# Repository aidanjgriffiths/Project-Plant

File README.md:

# Plantiful
#### A Powerful Embedded Monitoring Device for plant Enthusiasts
This page aims to document the source code, software and hardware incorporated in the development and production of the Plantiful prototype.

## Software
### Android Studio  
Used for developing a mobile app that will collect sensor data and provide information to the user regarding the state of their plants. 
Many people possess Android phones. Group members have experience programming in Java on this platform. 
### PHP Storm  
Modern PHP IDE for developing Web Applications within several Web Environment's. This provides our Users with a Convenient platform for viewing Plant Data, with regard to the health status of their plants, the weekly requirements from the User in terms of providing the appropriate nourishments for the Plants, and the projected requirement's in the future.
### MySQL Workbench
Interface directly to the Database hosted in the cloud, allowing for effective and simple queries and modifications to the Database
### AWS Lightsail
Web Sever Hosting Service on Amazon Web Services, which hosts the Virtual Web Server, running a Headless Ubuntu Instance, with a LAMP (LAMP) stack pre-installed on the operating system  
### AWS MySQL RDS
Relational Database Service for the Cloud MySQL Database, for access from the Web Application and Android Application. This is the central point for the back-end configuration of the MySQL Database Instance
### Arduino IDE 
IDE provides a coding platform for writing high level C/C++ based code that can be flashed to an Arduino board. 
Accessible coding platform. Runs on Windows. Basic setup and looping format. Many well-established libraries available. USB flashing. Debugging is simple using the provided serial terminal.
### AutoDesk Fusion 360 
Used for developing 3D designs for the hardware enclosure (prototype and final design). 
Accessible. At least one group member has experience developing models with this software. Parts can be assembled and animated. Enable direct export of 3D printing file. Schematic drawings are available for large scale production. 
### AutoDesk Eagle
Used for developing CAD schematic and printed circuit board designs for the embedded system final design. Program works in conjunction with Fusion 360 to purpose fit to the hardware shell.
### Cura 
Enables slicing and positioning of component pieces on 3D printing platform. 
Group member is in possession of this software and has experience using it for printing prototypes. 

## Hardware
### Uno R3 
Compact micro-processing unit with I/O ports for interfacing with moisture, temperature/humidity and light sensors. Minimal processing required except to transmit sensor data serially over Bluetooth.
Accessible, cost effective, and comes with an IDE that includes simplified coding functions for reading data from sensors and communicating serially with the proposed mobile application. Used for initial development, with later revisions using the same microcontroller (ATMEL ATMega328) in a bare configuration. 
### Moisture sensor 
DFRobot moisture sensor measures soil moisture, utilising an inbuilt transistor and associated discrete parts amplify a weak current between the probes into a 0-5v signal dependent on moisture. Will be used to determines if plant requires watering or is over-hydrated. 
Cheap, accurate and interfaces well with Arduino. No external libraries are required. 
### Temperature / Humidity sensor (DHT12)
Digital temperature and humidity sensor to determine ambient environmental parameters that determine the suitability of the conditions for optimal plant development. Highly reliable and fast response. -40 - 80C temperature range with error of +/- 0.5C, 0-100% humidity range with an error of 2-5% over the range. Easy to interface with Arduino with easy to use, highly available external libraries.
### Ambient light sensor (5kOhm Light Dependent Resistor)
Measures ambient light and reflects analog voltage to Arduino controller. Will be used to determine if the plant is receiving the correct amount of sunlight. 
Simple to use and interfaces relatively easily with Arduino requiring a single pull-up resistor as the only extra part. No additional libraries required, but basic calibration required.
### HC-05 Bluetooth module 
Enables Bluetooth connection with mobile device to communicate sensor data serially. 
Easy to setup and maintain a reliable connection with a mobile phone. Security is not a priority given the non-critical nature of the sensor data collected.

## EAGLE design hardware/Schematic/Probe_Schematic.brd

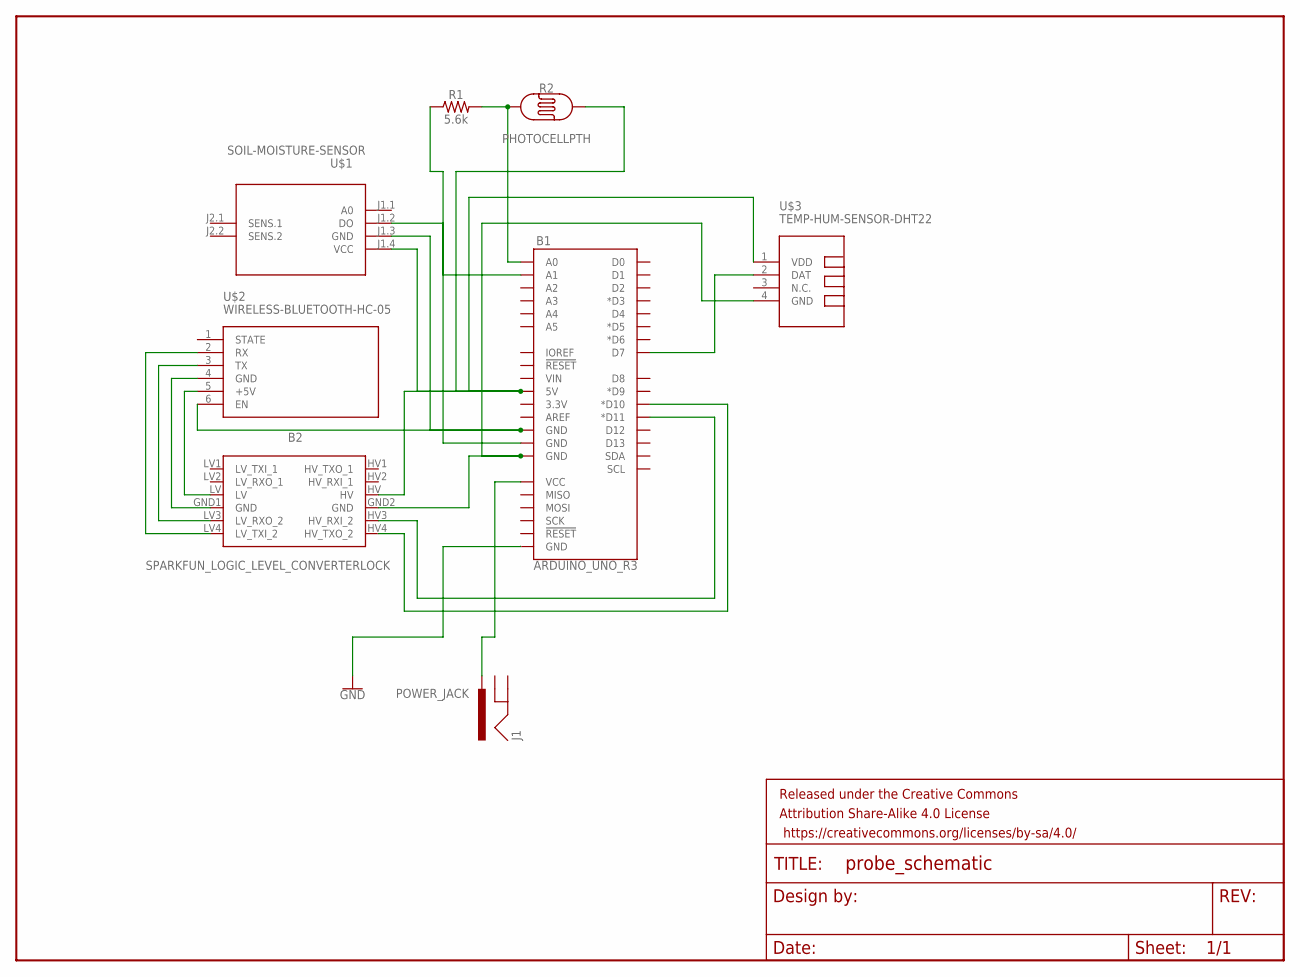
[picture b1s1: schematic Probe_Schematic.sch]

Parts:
B1: ARDUINO_UNO_R3; ARDUINO_R3
B2: SPARKFUN_LOGIC_LEVEL_CONVERTERLOCK; SPARKFUN_LOGIC_LEVEL_CONVERTER_LOCK
FRAME1: FRAME-LETTER; CREATIVE_COMMONS
J1: POWER_JACK; POWER_JACK_PTH
R1: 5.6k; 0603
R2: PHOTOCELLPTH; PHOTOCELL
U$1: SOIL-MOISTURE-SENSOR
U$2: WIRELESS-BLUETOOTH-HC-05
U$3: TEMP-HUM-SENSOR-DHT22

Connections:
GND: B1.GND@1 (GND)
unnamed: B1.GND@4 (GND), U$1.J1.3 (GND), U$2.6 (EN)
unnamed: B2.GND1 (GND), U$2.4 (GND)
unnamed: B2.LV, U$2.5 (+5V)
unnamed: B2.LV3 (LV_RXO_2), U$2.3 (TX)
unnamed: B2.LV4 (LV_TXI_2), U$2.2 (RX)
unnamed: B1.GND@2 (GND), B2.GND2 (GND), U$3.4 (GND)
unnamed: B1.GND@3 (GND), R1.1
unnamed: B1.D11 (*D11), B2.HV3 (HV_RXI_2)
unnamed: B1.D10 (*D10), B2.HV4 (HV_TXO_2)
unnamed: B1.D7, U$3.2 (DAT)
unnamed: B1.A1, U$1.J1.2 (DO)
unnamed: B1.VCC, J1.PWR
unnamed: B1.5V, B2.HV, R2.2, U$1.J1.4 (VCC), U$3.1 (VDD)
unnamed: B1.A0, R1.2, R2.1

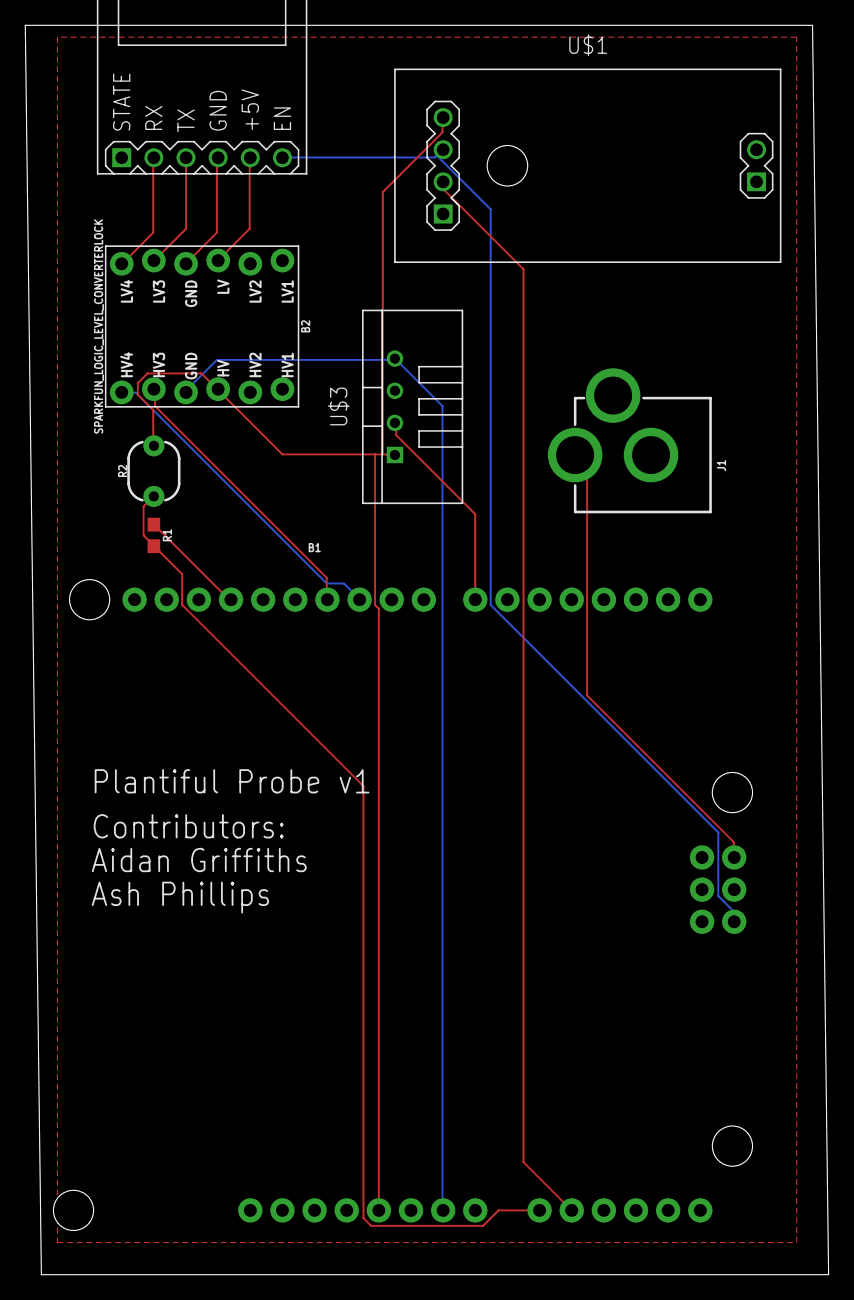
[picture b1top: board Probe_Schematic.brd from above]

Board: 2 copper layers, 63.5 x 98.7 mm, 9 parts (0 on the bottom side), 14 nets.

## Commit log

2020-08-07 Initial app commit
    Android app initial commit with splash screen, bluetooth connectivity and text-to-voice
2020-08-07 Added resources activity
    Links to 6 different resources on Australian flora
2020-08-07 Update AndroidManifest.xml
    updated the manifest to include the resources activity
2020-08-16 chore: Updated README Software and Hardware
2020-08-19 Added backend data base and monitoring
    Profiles and monitor activities added.
    Notification channel established for weekly notification to check on plants
    Camera, QR generator and reader included. Ability to add, delete profiles.
    Connecting to bluetooth shifted to montioring acitivity
2020-08-20 Information and help activities
    Added content to information and help activities
2020-08-23 FEAT: Add basic simulator functionality.
    Allow the generation of simulated values to help decouple the hardware and software development.
2020-08-26 chore: renamed several files to adhere to a consistent convention, removed unneccesary imports, redfined the file structure to improve consitency and design
2020-08-27 Testing and debugging
    Added camera permissions
2020-08-30 Added Main Structure of Plantiful Web
2020-08-30 Update README.md
    Added PHP Storm Blurb
2020-09-01 Added JQuery and QRCode Dependencies with Example
2020-09-03 Revert "chore: renamed several files to adhere to a consistent convention, removed unneccesary imports, redfined the file structure to improve consitency and design"
    This reverts commit 75622261d98e398c48d67b0120e4a7db74bda604.
2020-09-05 Added Database SQL Creation Script
2020-09-05 Added functionality to Establish the Database Connection
2020-09-05 Modified SQL Creation Script and Added Stored Procedures
2020-09-05 Removed Old DB Connector (DAL)
2020-09-06 Removed Unnecessary Files
2020-09-06 Modified SQL Creation Script to Support User Changes
2020-09-06 Modified User Model
2020-09-06 Added functionality for Android-Web Account Association
2020-09-06 Added Android Web API Test Application
2020-09-08 New Dev branch changes
2020-09-08 FEAT: Testers for invidual hardware components
2020-09-08 FEAT: First cut of main hardware sketch
2020-09-08 DOC: Bill of Materials
2020-09-08 FEAT: Initial hardware code
2020-09-08 Font Changes
2020-09-09 Added plant states
2020-09-09 Modified SQL DB Creation Script to Add Measurement/User Association
2020-09-09 Normalised slider values and added webserver connectivity
2020-09-10 Added the Main Page UI and the Registration Page UI (and the relevant resources)
2020-09-11 Added Full Names of Development Team to Registration Page
2020-09-11 Modified Index Validation
2020-09-11 Added Raw Query for Debugging Purposes
2020-09-11 Refactored Index Page
2020-09-11 Modified Test Functionality to work with RQ API
2020-09-11 Fixed Index References
2020-09-15 Update README.md
    Added MySQL Workbench, and AWS Stack
2020-09-15 FEAT: Add serial debug functionality
    Define DEBUG to allow simultaneous sniffing of hardware input before it is sent out over bluetooth.
2020-09-15 FEAT: Limit simulator values
    Set sensible upper and lower values for simulator variables.
2020-09-15 Minor adjustment to app monitoring
2020-09-16 refactor: readabiliy changes of simulator script
    Hey, @AshPhillips2786, I went ahead and refactored the code to address the comments I made on the review. I since I don't have the system with me its up to you on whether you want to keep these chang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
2020-09-16 fix: exclusive random function
    I just realised that the random functions maximum parameter is exclusive so I'm just fixing my previous commit.
2020-09-16 Added Graphing Support and Framework for Web App Functions
2020-09-16 Refined min/max plant profile values
    - min/max profile update
    - increased Serial read delay to 300ms
    - provided debugging views of Serial read and string parsing
2020-09-16 doc: adding AutoDesk Eagle to documenation
    Adding extra program to the Software page.
2020-09-18 Added comments
2020-09-19 Revert readability changes
    FIX: Revert previous readability changes
2020-09-19 DOC: Update README hardware details
    Update the main README with more accurate details of the hardware used in the prototype.
2020-09-19 CHORE: Clean up folder structure
    Clean up and rename hardware folders prior to project completion.
2020-09-19 FEAT: Add visual feedback on read
    Add visual feedback on sensor read request
2020-09-19 CHORE: Clean out testing code
    Remove accidentally committed testing code.
2020-09-19 CHORE: Improve code structure
    Swap from if to switch to allow easier future improvements.
2020-09-19 DOC: Add testers documentation
    Basic documentation on the case and use of the Testers documentation for repeat hardware testing and validation.
2020-09-20 Websync profiles and sensor data
2020-09-20 Finishing touches...register user to web
2020-09-21 FEAT: Early design documentation
    Fritzing diagrams and JPG's of the first iterations of the hardware and the Tester layouts.
2020-09-22 Allow visual read indication (#37)
    * CHORE: Clean up folder structure
    Clean up and rename hardware folders prior to project completion.
    * FEAT: Add visual feedback on read
    Add visual feedback on sensor read request
    * CHORE: Clean out testing code
    Remove accidentally committed testing code.
2020-09-22 Revert "Allow visual read indication (#37)"
    This reverts commit 4410729191dba5b457dad01aced417a1986ac017.
2020-09-22 Revert "Revert "Allow visual read indication""
2020-09-23 Modified Design of Registration Page and Completed Registration Sync with Android App
2020-09-23 Added Infrastructure Model and Redirect when user has Registered
2020-09-24 Added Measurement Avg Screen & Measurements Screen with Visualisations
2020-09-24 Modified Model include statements due to Server-Side 500 Error
2020-09-25 Hardware design notes
    Main design notes on the bare microcontroller version and some minor updates to tester documentation.
2020-09-25 feat: initial models and drawings of hardware shell
2020-09-25 schematic and pcbs
2020-09-27 Minor code rework

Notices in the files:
parts and their libraries:
SparkFun-Boards: Licensing: Creative Commons ShareAlike 4.0 International - https://creativecommons.org/licenses/by-sa/4.0
SparkFun-Aesthetics: Released under the Creative Commons Attribution Share-Alike 4.0 License
SparkFun-Aesthetics: https://creativecommons.org/licenses/by-sa/4.0
